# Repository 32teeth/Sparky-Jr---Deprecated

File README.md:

Sparky Jr
=========

Sparky Jr is a programmable RGB LED mod companion light up activation controller for arcade pushbuttons on gaming fightsticks

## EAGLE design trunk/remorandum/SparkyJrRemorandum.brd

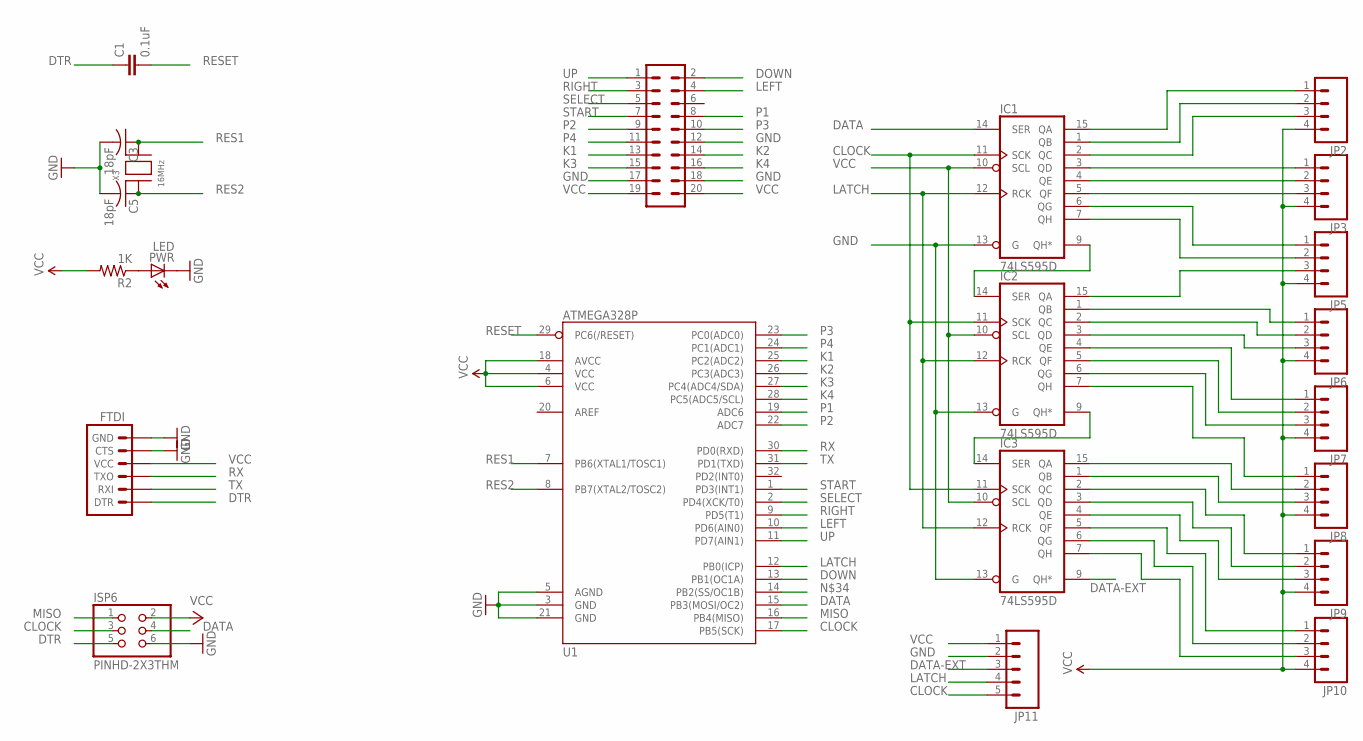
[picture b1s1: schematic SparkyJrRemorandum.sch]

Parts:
C1: 0.1uF; 0805
C3, C5: 18pF; C0805K
FTDI: ARDUINO_SERIAL_PROGRAMPTH; 1X06
IC1, IC2, IC3: 74LS595D; SO16
ISP6: PINHD-2X3THM; 2X03
JP2, JP3, JP5, JP6, JP7, JP8, JP9, JP10: M04PTH; 1X04
JP11: M05PTH; 1X05
PWR: LED; CHIPLED_0805
R2: 1K; R0805
U1: ATMEGA328P; TQFP32-08
U$1: M10X2NOSILK; 2X10_NOSILK
X3: 16MHz; NX5032

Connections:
CLOCK: IC1.11 (SCK), IC2.11 (SCK), IC3.11 (SCK), ISP6.3, JP11.5, U1.17 (PB5(SCK))
DATA: IC1.14 (SER), ISP6.4, U1.15 (PB3(MOSI/OC2))
DATA-EXT: IC3.9 (QH*), JP11.3
DOWN: U1.13 (PB1(OC1A)), U$1.2
DTR: C1.1, FTDI.1 (DTR), ISP6.5
GND: C3.2, C5.2, FTDI.5 (CTS), FTDI.6 (GND), IC1.8 (GND), IC1.13 (G), IC2.8 (GND), IC2.13 (G), IC3.8 (GND), IC3.13 (G), ISP6.6, JP11.2, PWR.C, U1.3 (GND), U1.5 (AGND), U1.21 (GND), U$1.12, U$1.17, U$1.18
K1: U1.25 (PC2(ADC2)), U$1.13
K2: U1.26 (PC3(ADC3)), U$1.14
K3: U1.27 (PC4(ADC4/SDA)), U$1.15
K4: U1.28 (PC5(ADC5/SCL)), U$1.16
LATCH: IC1.12 (RCK), IC2.12 (RCK), IC3.12 (RCK), JP11.4, U1.12 (PB0(ICP))
LEFT: U1.10 (PD6(AIN0)), U$1.4
MISO: ISP6.1, U1.16 (PB4(MISO))
unnamed: PWR.A, R2.1
unnamed: IC1.9 (QH*), IC2.14 (SER)
unnamed: IC2.9 (QH*), IC3.14 (SER)
unnamed: IC1.15 (QA), JP2.1
unnamed: IC1.1 (QB), JP2.2
unnamed: IC1.2 (QC), JP2.3
unnamed: IC1.3 (QD), JP3.1
unnamed: IC1.4 (QE), JP3.2
unnamed: IC1.5 (QF), JP3.3
unnamed: IC1.6 (QG), JP5.1
unnamed: IC1.7 (QH), JP5.2
unnamed: IC2.15 (QA), JP5.3
unnamed: IC2.1 (QB), JP6.1
unnamed: IC2.2 (QC), JP6.2
unnamed: IC2.3 (QD), JP6.3
unnamed: IC2.4 (QE), JP7.1
unnamed: IC2.5 (QF), JP7.2
unnamed: IC2.6 (QG), JP7.3
unnamed: IC2.7 (QH), JP8.1
unnamed: IC3.15 (QA), JP8.2
unnamed: IC3.1 (QB), JP8.3
unnamed: IC3.2 (QC), JP9.1
unnamed: IC3.3 (QD), JP9.2
unnamed: IC3.4 (QE), JP9.3
unnamed: IC3.5 (QF), JP10.1
unnamed: IC3.6 (QG), JP10.2
unnamed: IC3.7 (QH), JP10.3
P1: U1.19 (ADC6), U$1.8
P2: U1.22 (ADC7), U$1.9
P3: U1.23 (PC0(ADC0)), U$1.10
P4: U1.24 (PC1(ADC1)), U$1.11
RES1: C3.1, U1.7 (PB6(XTAL1/TOSC1)), X3.P$2
RES2: C5.1, U1.8 (PB7(XTAL2/TOSC2)), X3.P$1
RESET: C1.2, U1.29 (PC6(/RESET))
RIGHT: U1.9 (PD5(T1)), U$1.3
RX: FTDI.3 (TXO), U1.30 (PD0(RXD))
SELECT: U1.2 (PD4(XCK/T0)), U$1.5
START: U1.1 (PD3(INT1)), U$1.7
TX: FTDI.2 (RXI), U1.31 (PD1(TXD))
UP: U1.11 (PD7(AIN1)), U$1.1
VCC: FTDI.4 (VCC), IC1.10 (SCL), IC1.16 (VCC), IC2.10 (SCL), IC2.16 (VCC), IC3.10 (SCL), IC3.16 (VCC), ISP6.2, JP2.4, JP3.4, JP5.4, JP6.4, JP7.4, JP8.4, JP9.4, JP10.4, JP11.1, R2.2, U1.4 (VCC), U1.6 (VCC), U1.18 (AVCC), U$1.19, U$1.20

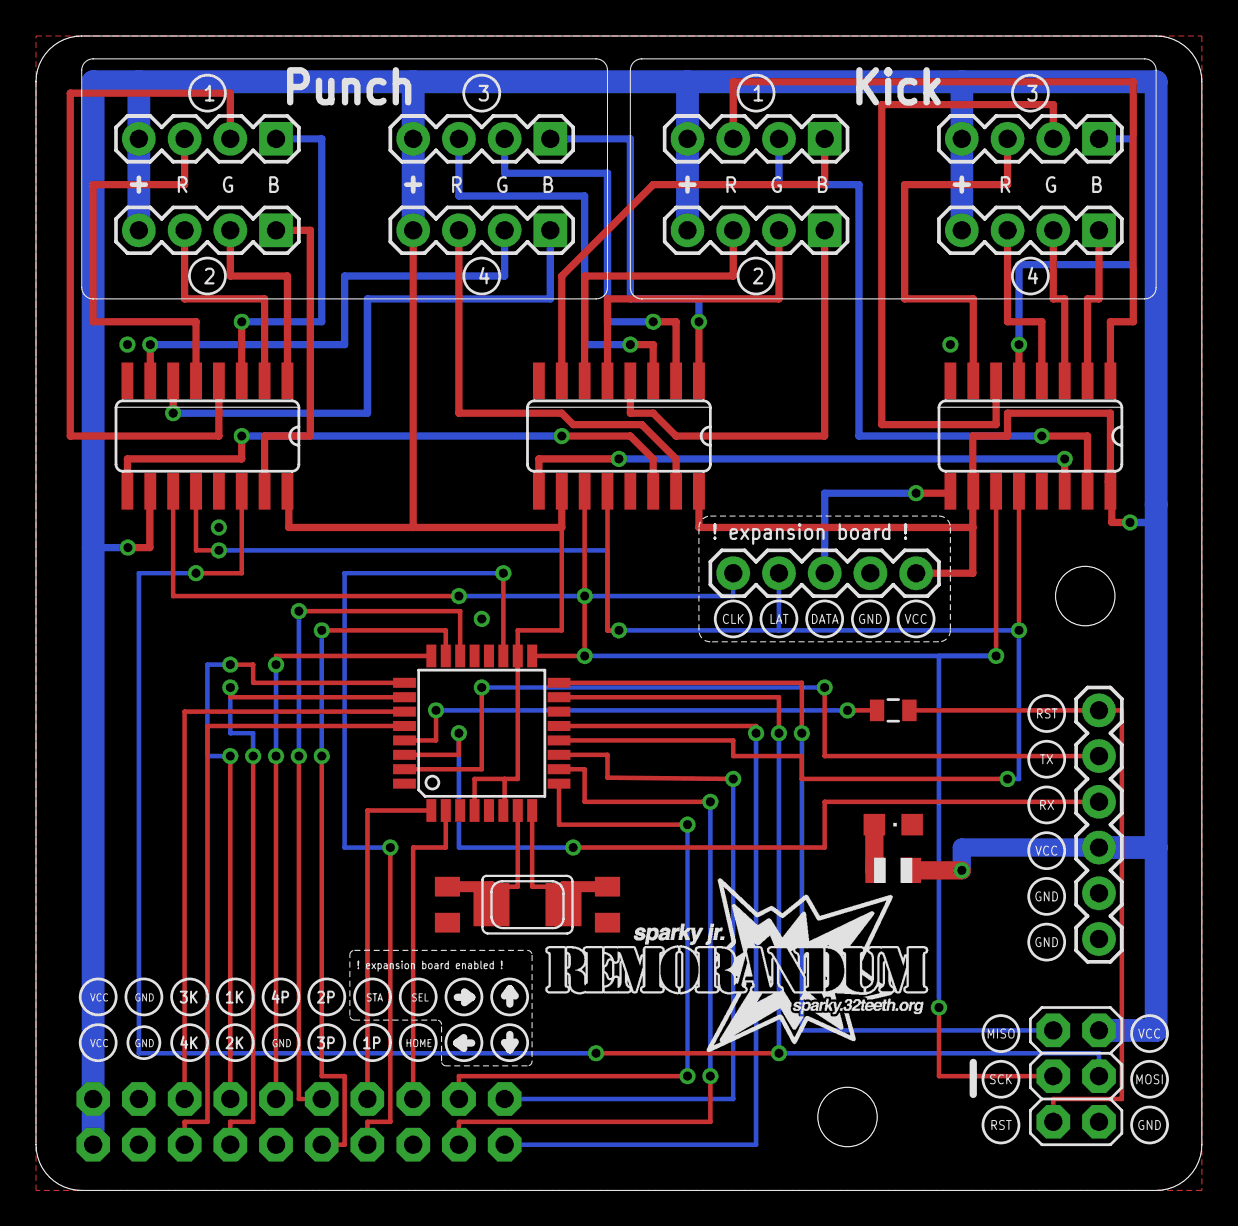
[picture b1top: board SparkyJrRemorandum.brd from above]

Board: 2 copper layers, 64.8 x 64.1 mm, 24 parts (0 on the bottom side), 54 nets.

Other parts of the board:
JP1, JP4: STAND-OFF

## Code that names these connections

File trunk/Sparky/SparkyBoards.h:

/*
  @commonPins assigned from #define board index in boards array above
  @colorPins assigned from #define board index in boards array above
  @buttonPins assigned from #define board index in boards array above
*/

//  Sparky Jr USB
//----------------------------------------------------
#ifdef SparkyJrUSB
  int commonPins[outputs] = {23,22,21,20,19,18,13,5};
  int colorPins[colors] = {9,10,11};
  int buttonPins[inputs] = {3,2,0,1,4,12,6,8};
  int configLED = 7;
#endif
//----------------------------------------------------
//
 
//----------------------------------------------------

//  Sparky FTDI
//----------------------------------------------------
#ifdef SparkyJrFTDI
  int commonPins[outputs] = {18,17,16,15,14,13,12,8};
  int colorPins[colors] = {9,10,11};
  int buttonPins[inputs] = {0,1,2,3,4,5,6,7};
  int configLED = 19;  
#endif
//----------------------------------------------------


//  Sparky Shield
//----------------------------------------------------
/*
// ATMEL ATMEGA8 & 168 / ARDUINO
//
//                  +-\/-+
//            PC6  1|    |28  PC5 (AI 5 / D19)
//      (D 0) PD0  2|    |27  PC4 (AI 4 / D18)
//      (D 1) PD1  3|    |26  PC3 (AI 3 / D17)
//      (D 2) PD2  4|    |25  PC2 (AI 2 / D16)
// PWM+ (D 3) PD3  5|    |24  PC1 (AI 1 / D15)
//      (D 4) PD4  6|    |23  PC0 (AI 0 / D14)
//            VCC  7|    |22  GND
//            GND  8|    |21  AREF
//            PB6  9|    |20  AVCC
//            PB7 10|    |19  PB5 (D 13)
// PWM+ (D 5) PD5 11|    |18  PB4 (D 12)
// PWM+ (D 6) PD6 12|    |17  PB3 (D 11) PWM
//      (D 7) PD7 13|    |16  PB2 (D 10) PWM
//      (D 8) PB0 14|    |15  PB1 (D 9) PWM
//                  +----+
*/
#ifdef SparkyJrShield
  int commonPins[outputs] = {18,17,16,15,14,13,12,8};
  /*
        
  */
  int colorPins[colors] = {9,10,11};
  int buttonPins[inputs] = {0,1,2,3,4,5,6,7};
  int configLED = 19;
#endif
//----------------------------------------------------  

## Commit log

2012-08-03 Added core files
2012-08-31 Replaced files from repo
2012-09-11 Added Wii Classic Controller
    Added Wii Classic Controller to library
2012-09-25 Clock Change
    Clock Change
2012-10-10 Added remorandum
    Added remorandum
2013-11-01 Updated some libraries to Processing 2.0
    Same as above
